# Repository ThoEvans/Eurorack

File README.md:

# Eurorack
Hardware design for Eurorack modular synthesizers

These files contain schematics (.sch) and board layouts (.brd) from AutoDesk Eagle.
Please note that these are simple projects or ideas that are at various stages of completion.

To download an individual file, right click "Raw" and choose "Save link as..."

PCBs available at Pusherman Productions! [Dual LPF PCBs](https://pushermanproductions.com/product/thomas-evans-dual-lp-vcf-pcb-set-fr4-panel/)

## Any questions or comments can be sent to thoevans1994@gmail(dot)com.

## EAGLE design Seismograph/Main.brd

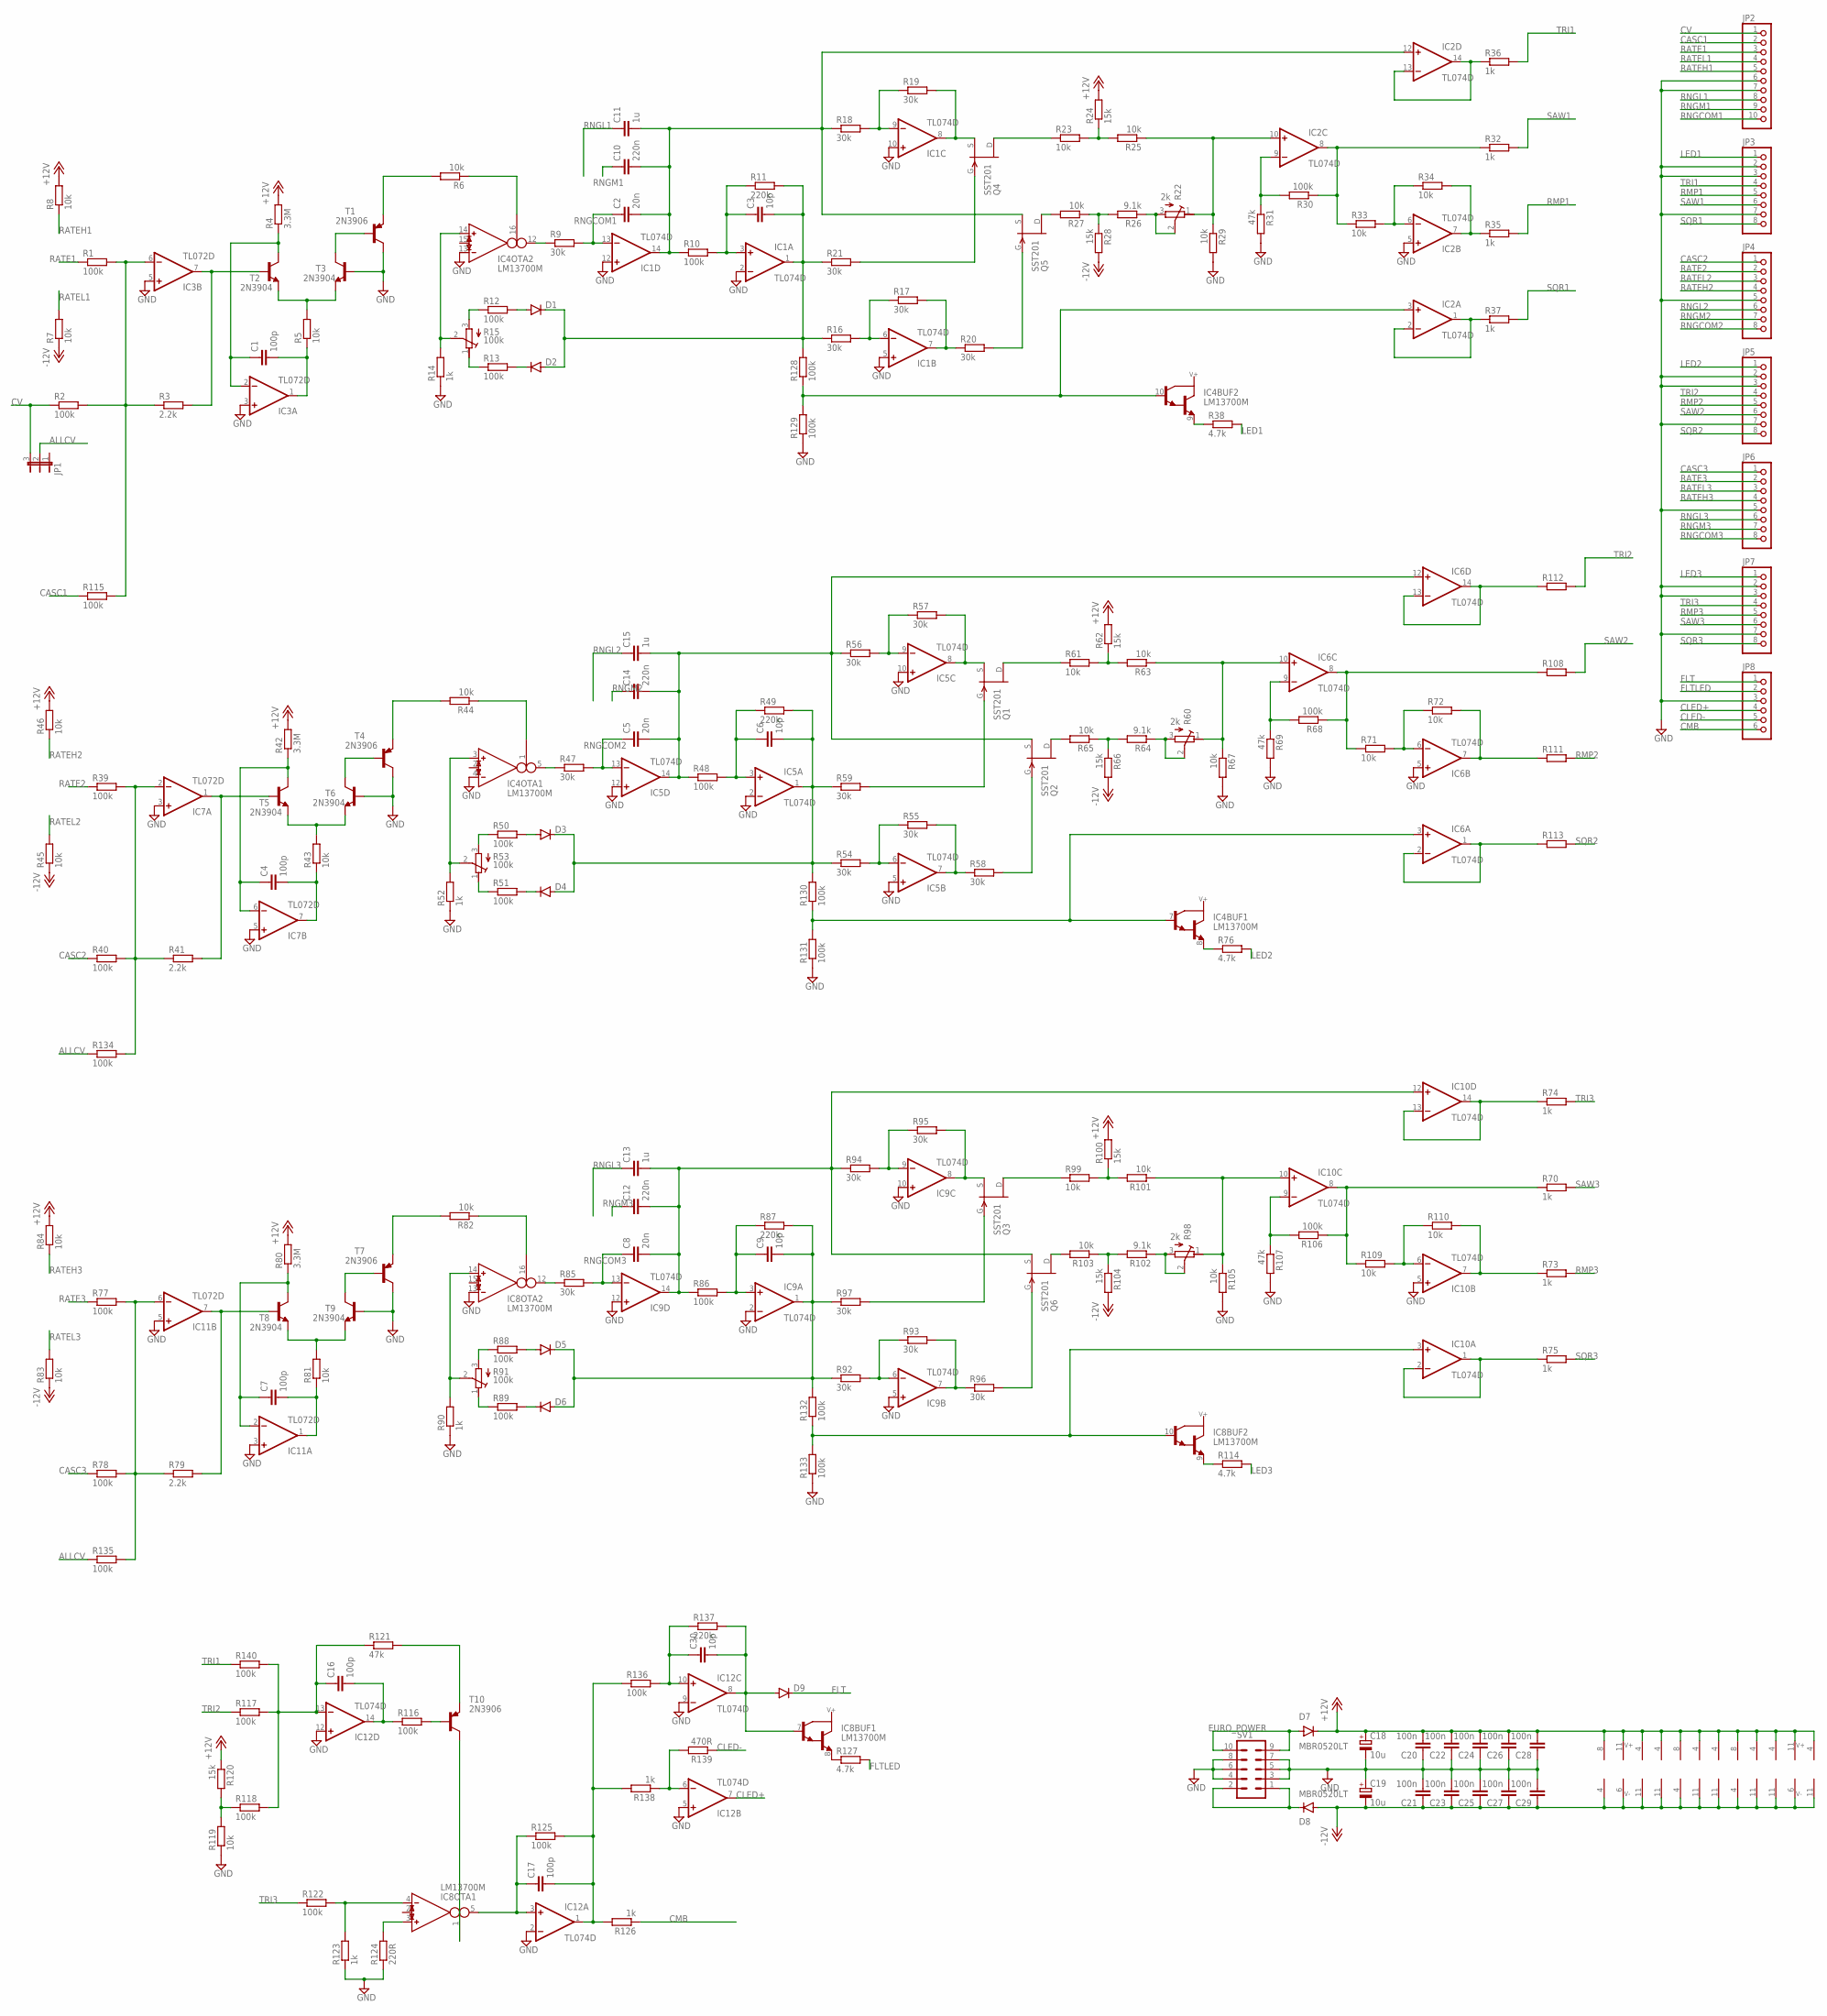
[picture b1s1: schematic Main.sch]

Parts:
C1, C4, C7, C16, C17: 100p; C0805
C2, C5, C8: 20n; C050-025X075
C3, C6, C9, C30: 10p; C0805
C10, C12, C14: 220n; C050-035X075
C11, C13, C15: 1u; C050-045X075
C18, C19: 10u; E2,5-5
C20, C21, C22, C23, C24, C25, C26, C27, C28, C29: 100n; C0805
D1, D2, D3, D4, D5, D6, D9: DIODE-SOD123; SOD123
D7, D8: MBR0520LT; SOD123
IC1, IC2, IC5, IC6, IC9, IC10, IC12: TL074D; SO14
IC3, IC7, IC11: TL072D; SO08
IC4, IC8: LM13700M; SO16
JP1: JP2E; JP2
JP2: PINHD-1X10; 1X10
JP3, JP4, JP5, JP6, JP7: PINHD-1X8; 1X08
JP8: PINHD-1X6; 1X06
Q1, Q2, Q3, Q4, Q5, Q6: SST201; SOT23
R1, R2, R10, R12, R13, R30, R39, R40, R48, R50, R51, R68, R77, R78, R86, R88, R89, R106, R115, R116, R117, R118, R122, R125, R128, R129, R130, R131, R132, R133, R134, R135, R136, R140: 100k; R0805
R3, R41, R79: 2.2k; R0805
R4, R42, R80: 3.3M; R0805
R5, R6, R7, R8, R23, R25, R27, R29, R33, R34, R43, R44, R45, R46, R61, R63, R65, R67, R71, R72, R81, R82, R83, R84, R99, R101, R103, R105, R109, R110, R119: 10k; R0805
R9, R16, R17, R18, R19, R20, R21, R47, R54, R55, R56, R57, R58, R59, R85, R92, R93, R94, R95, R96, R97: 30k; R0805
R11, R49, R87, R137: 220k; R0805
R14, R32, R35, R36, R37, R52, R70, R73, R74, R75, R90, R123, R126, R138: 1k; R0805
R15, R53, R91: 100k; RTRIMT93XB
R22, R60, R98: 2k; RTRIMT93XB
R24, R28, R62, R66, R100, R104, R120: 15k; R0805
R26, R64, R102: 9.1k; R0805
R31, R69, R107, R121: 47k; R0805
R38, R76, R114, R127: 4.7k; R0805
R108, R111, R112, R113: R-EU_R0805; R0805
R124: 220R; R0805
R139: 470R; R0805
SV1: EURO_POWER; EURO_PWR_HEADER_FAT
T1, T4, T7, T10: 2N3906; SOT23-BEC
T2, T3, T5, T6, T8, T9: 2N3904; SOT23-BEC

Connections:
+12V: C18.+, C20.2, C22.2, C24.2, C26.2, C28.2, D7.C, IC1.4 (V+), IC2.4 (V+), IC3.8 (V+), IC4.11 (V+), IC5.4 (V+), IC6.4 (V+), IC7.8 (V+), IC8.11 (V+), IC9.4 (V+), IC10.4 (V+), IC11.8 (V+), IC12.4 (V+), R4.2, R8.2, R24.2, R42.2, R46.2, R62.2, R80.2, R84.2, R100.2, R120.1
-12V: C19.-, C21.1, C23.1, C25.1, C27.1, C29.1, D8.A, IC1.11 (V-), IC2.11 (V-), IC3.4 (V-), IC4.6 (V-), IC5.11 (V-), IC6.11 (V-), IC7.4 (V-), IC8.6 (V-), IC9.11 (V-), IC10.11 (V-), IC11.4 (V-), IC12.11 (V-), R7.1, R28.2, R45.1, R66.2, R83.1, R104.2
ALLCV: JP1.2, R134.1, R135.1
CASC1: JP2.2, R115.1
CASC2: JP4.1, R40.1
CASC3: JP6.1, R78.1
CLED+: IC12.7 (OUT), JP8.4
CLED-: JP8.5, R139.1
CMB: JP8.6, R126.1
CV: JP1.3, JP2.1, R2.1
FLT: D9.C, JP8.1
FLTLED: JP8.2, R127.2
GND: C18.-, C19.+, C20.1, C21.2, C22.1, C23.2, C24.1, C25.2, C26.1, C27.2, C28.1, C29.2, IC1.2 (-IN), IC1.5 (+IN), IC1.10 (+IN), IC1.12 (+IN), IC2.5 (+IN), IC3.3 (+IN), IC3.5 (+IN), IC4.4 (IN_N), IC4.13 (IN_N), IC5.2 (-IN), IC5.5 (+IN), IC5.10 (+IN), IC5.12 (+IN), IC6.5 (+IN), IC7.3 (+IN), IC7.5 (+IN), IC8.13 (IN_N), IC9.2 (-IN), IC9.5 (+IN), IC9.10 (+IN), IC9.12 (+IN), IC10.5 (+IN), IC11.3 (+IN), IC11.5 (+IN), IC12.2 (-IN), IC12.5 (+IN), IC12.9 (-IN), IC12.12 (+IN), JP2.6, JP2.7, JP3.2, JP3.3, JP3.7, JP4.5, JP5.2, JP5.3, JP5.7, JP6.5, JP7.2, JP7.3, JP7.7, JP8.3, R14.1, R29.2, R31.2, R52.1, R67.2, R69.2, R90.1, R105.2, R107.2, R119.1, R123.1, R124.1, R129.1, R131.1, R133.1, SV1.3, SV1.4, SV1.5, SV1.6, SV1.7, SV1.8, T1.C, T3.B, T4.C, T6.B, T7.C, T9.B
LED1: JP3.1, R38.2
LED2: JP5.1, R76.2
LED3: JP7.1, R114.2
unnamed: IC8.8 (E), R127.1
unnamed: C30.1, IC12.10 (+IN), R136.2, R137.1
unnamed: C30.2, D9.A, IC8.7 (B), IC12.8 (OUT), R137.2
unnamed: IC3.6 (-IN), R1.2, R2.2, R3.1, R115.2
unnamed: R5.2, T2.E, T3.E
unnamed: IC3.7 (OUT), R3.2, T2.B
unnamed: C1.1, IC3.2 (-IN), R4.1, T2.C
unnamed: C1.2, IC3.1 (OUT), R5.1
unnamed: T1.B, T3.C
unnamed: D2.C, R13.2
unnamed: R6.2, T1.E
unnamed: IC12.6 (-IN), R138.1, R139.2
unnamed: C16.1, IC12.13 (-IN), R117.2, R118.2, R121.1, R140.2
unnamed: D1.A, R12.2
unnamed: IC4.12 (OUT), R9.1
unnamed: C2.2, C10.2, C11.2, IC1.14 (OUT), IC2.12 (+IN), Q5.2 (S), R10.1, R18.1
unnamed: C3.1, IC1.3 (+IN), R10.2, R11.1
unnamed: IC2.3 (+IN), IC4.10 (B), R128.1, R129.2
unnamed: R12.1, R15.3 (A)
unnamed: R13.1, R15.1 (E)
unnamed: IC4.14 (IN_P), R14.2, R15.2 (S)
unnamed: IC1.6 (-IN), R16.2, R17.1
unnamed: IC1.7 (OUT), R17.2, R20.1
unnamed: IC1.9 (-IN), R18.2, R19.1
unnamed: IC1.8 (OUT), Q4.2 (S), R19.2
unnamed: Q4.3 (G), R21.2
unnamed: Q5.3 (G), R20.2
unnamed: Q4.1 (D), R23.1
unnamed: Q5.1 (D), R27.2
unnamed: R26.2, R27.1, R28.1
unnamed: R23.2, R24.1, R25.2
unnamed: IC2.10 (+IN), R22.1 (E), R25.1, R29.1
unnamed: R22.2 (S), R22.3 (A), R26.1
unnamed: IC7.2 (-IN), R39.2, R40.2, R41.1, R134.2
unnamed: IC2.9 (-IN), R30.2, R31.1
unnamed: IC2.8 (OUT), R30.1, R32.1, R33.1
unnamed: IC2.7 (OUT), R34.2, R35.1
unnamed: IC2.6 (-IN), R33.2, R34.1
unnamed: IC2.13 (-IN), IC2.14 (OUT), R36.1
unnamed: IC2.1 (OUT), IC2.2 (-IN), R37.1
unnamed: IC7.1 (OUT), R41.2, T5.B
unnamed: C4.1, IC7.6 (-IN), R42.1, T5.C
unnamed: IC4.9 (E), R38.1
unnamed: IC4.16 (I_BIAS), R6.1
unnamed: R43.2, T5.E, T6.E
unnamed: C4.2, IC7.7 (OUT), R43.1
unnamed: T4.B, T6.C
unnamed: D4.C, R51.2
unnamed: D3.A, R50.2
unnamed: IC4.5 (OUT), R47.1
unnamed: C5.2, C14.2, C15.2, IC5.14 (OUT), IC6.12 (+IN), Q2.2 (S), R48.1, R56.1
unnamed: C6.1, IC5.3 (+IN), R48.2, R49.1
unnamed: IC4.7 (B), IC6.3 (+IN), R130.1, R131.2
unnamed: R50.1, R53.3 (A)
unnamed: R51.1, R53.1 (E)
unnamed: IC4.3 (IN_P), R52.2, R53.2 (S)
unnamed: IC5.6 (-IN), R54.2, R55.1
unnamed: IC5.7 (OUT), R55.2, R58.1
unnamed: IC5.9 (-IN), R56.2, R57.1
unnamed: IC5.8 (OUT), Q1.2 (S), R57.2
unnamed: Q1.3 (G), R59.2
unnamed: Q2.3 (G), R58.2
unnamed: Q1.1 (D), R61.1
unnamed: Q2.1 (D), R65.2
unnamed: R64.2, R65.1, R66.1
unnamed: R61.2, R62.1, R63.2
unnamed: IC6.10 (+IN), R60.1 (E), R63.1, R67.1
unnamed: R60.2 (S), R60.3 (A), R64.1
unnamed: IC6.9 (-IN), R68.2, R69.1
unnamed: IC6.8 (OUT), R68.1, R71.1, R108.1
unnamed: IC6.7 (OUT), R72.2, R111.1
unnamed: IC6.6 (-IN), R71.2, R72.1
unnamed: IC6.13 (-IN), IC6.14 (OUT), R112.1
unnamed: IC6.1 (OUT), IC6.2 (-IN), R113.1
unnamed: R118.1, R119.2, R120.2
unnamed: IC4.8 (E), R76.1
unnamed: R44.2, T4.E
unnamed: IC4.1 (I_BIAS), R44.1
unnamed: IC11.6 (-IN), R77.2, R78.2, R79.1, R135.2
unnamed: IC11.7 (OUT), R79.2, T8.B
unnamed: C7.1, IC11.2 (-IN), R80.1, T8.C
unnamed: R81.2, T8.E, T9.E
unnamed: C7.2, IC11.1 (OUT), R81.1
unnamed: T7.B, T9.C
unnamed: D6.C, R89.2
unnamed: D5.A, R88.2
unnamed: IC8.12 (OUT), R85.1
unnamed: C8.2, C12.2, C13.2, IC9.14 (OUT), IC10.12 (+IN), Q6.2 (S), R86.1, R94.1
unnamed: C9.1, IC9.3 (+IN), R86.2, R87.1
unnamed: IC8.10 (B), IC10.3 (+IN), R132.1, R133.2
unnamed: R88.1, R91.3 (A)
unnamed: R89.1, R91.1 (E)
unnamed: IC8.14 (IN_P), R90.2, R91.2 (S)
unnamed: IC9.6 (-IN), R92.2, R93.1
unnamed: IC9.7 (OUT), R93.2, R96.1
unnamed: IC9.9 (-IN), R94.2, R95.1
unnamed: IC9.8 (OUT), Q3.2 (S), R95.2
unnamed: Q3.3 (G), R97.2
unnamed: Q6.3 (G), R96.2
unnamed: Q3.1 (D), R99.1
unnamed: Q6.1 (D), R103.2
unnamed: R102.2, R103.1, R104.1
unnamed: R99.2, R100.1, R101.2
unnamed: IC10.10 (+IN), R98.1 (E), R101.1, R105.1
unnamed: R98.2 (S), R98.3 (A), R102.1
unnamed: IC10.9 (-IN), R106.2, R107.1
unnamed: IC10.8 (OUT), R70.1, R106.1, R109.1
unnamed: IC10.7 (OUT), R73.1, R110.2
unnamed: IC10.6 (-IN), R109.2, R110.1
unnamed: IC10.13 (-IN), IC10.14 (OUT), R74.1
unnamed: IC10.1 (OUT), IC10.2 (-IN), R75.1
unnamed: IC8.9 (E), R114.1
unnamed: R82.2, T7.E
unnamed: IC8.16 (I_BIAS), R82.1
unnamed: C16.2, IC12.14 (OUT), R116.1
unnamed: R116.2, T10.B
unnamed: R121.2, T10.E
unnamed: IC8.1 (I_BIAS), T10.C
unnamed: IC8.3 (IN_P), R124.2
unnamed: C17.2, IC12.1 (OUT), R125.2, R126.2, R136.1, R138.2
unnamed: IC8.4 (IN_N), R122.2, R123.2
unnamed: C17.1, IC8.5 (OUT), IC12.3 (+IN), R125.1
unnamed: C9.2, D5.C, D6.A, IC9.1 (OUT), R87.2, R92.1, R97.1, R132.2
unnamed: C6.2, D3.C, D4.A, IC5.1 (OUT), R49.2, R54.1, R59.1, R130.2
unnamed: C3.2, D1.C, D2.A, IC1.1 (OUT), R11.2, R16.1, R21.1, R128.2
unnamed: D7.A, SV1.9, SV1.10
unnamed: D8.C, SV1.1, SV1.2
RATE1: JP2.3, R1.1
RATE2: JP4.2, R39.1
RATE3: JP6.2, R77.1
RATEH1: JP2.5, R8.1
RATEH2: JP4.4, R46.1
RATEH3: JP6.4, R84.1
RATEL1: JP2.4, R7.2
RATEL2: JP4.3, R45.2
RATEL3: JP6.3, R83.2
RMP1: JP3.5, R35.2
RMP2: JP5.5, R111.2
RMP3: JP7.5, R73.2
RNGCOM1: C2.1, IC1.13 (-IN), JP2.10, R9.2
RNGCOM2: C5.1, IC5.13 (-IN), JP4.8, R47.2
RNGCOM3: C8.1, IC9.13 (-IN), JP6.8, R85.2
RNGL1: C11.1, JP2.8
RNGL2: C15.1, JP4.6
RNGL3: C13.1, JP6.6
RNGM1: C10.1, JP2.9
RNGM2: C14.1, JP4.7
RNGM3: C12.1, JP6.7
SAW1: JP3.6, R32.2
SAW2: JP5.6, R108.2
SAW3: JP7.6, R70.2
SQR1: JP3.8, R37.2
SQR2: JP5.8, R113.2
SQR3: JP7.8, R75.2
TRI1: JP3.4, R36.2, R140.1
TRI2: JP5.4, R112.2, R117.1
TRI3: JP7.4, R74.2, R122.1

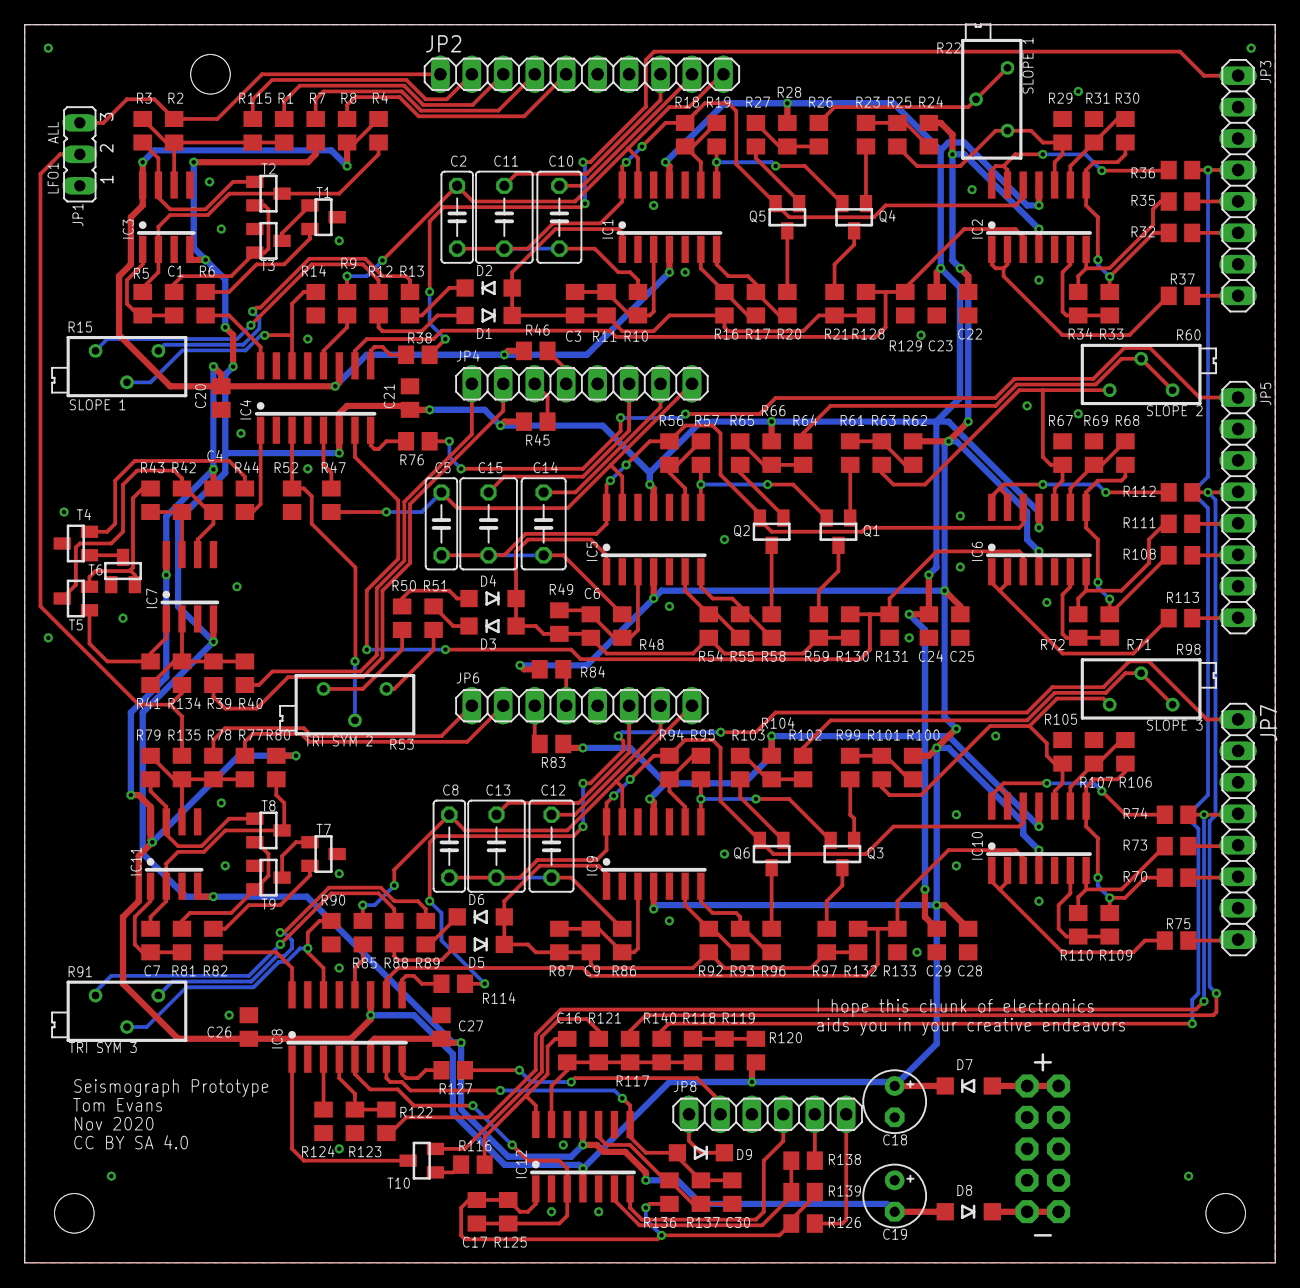
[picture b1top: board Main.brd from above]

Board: 2 copper layers, 101.0 x 100.0 mm, 216 parts (1 on the bottom side), 173 nets.

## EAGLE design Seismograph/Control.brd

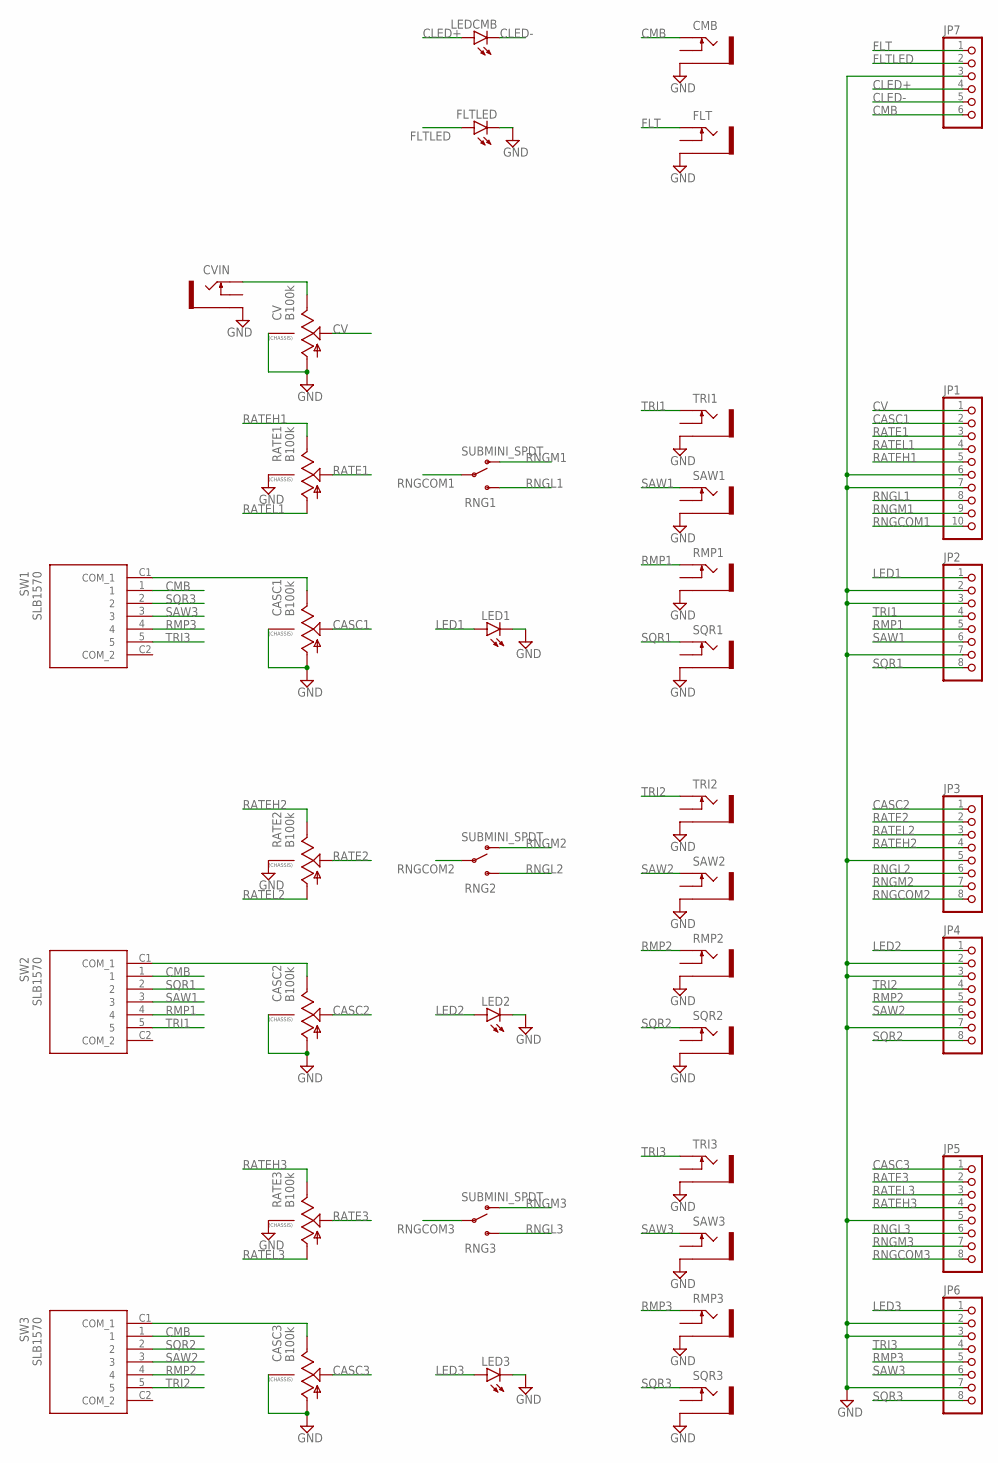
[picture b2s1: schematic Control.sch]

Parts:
CASC1, CASC2, CASC3: B100k; 9MM_SNAP-IN_POT
CMB: THONKICONNNEW; WQP-PJ301M-12_JACK
CV: B100k; 9MM_SNAP-IN_POT
CVIN: THONKICONNNEW; WQP-PJ301M-12_JACK
FLT: THONKICONNNEW; WQP-PJ301M-12_JACK
FLTLED: LED3MM
JP1: PINHD-1X10; 1X10
JP2, JP3, JP4, JP5, JP6: PINHD-1X8; 1X08
JP7: PINHD-1X6; 1X06
LED1, LED2, LED3: LED3MM
LEDCMB: LED3MM
RATE1, RATE2, RATE3: B100k; 9MM_SNAP-IN_POT
RMP1, RMP2, RMP3: THONKICONNNEW; WQP-PJ301M-12_JACK
RNG1, RNG2, RNG3: SUBMINI_SPDT; SUBMINI_TOGGLE
SAW1, SAW2, SAW3: THONKICONNNEW; WQP-PJ301M-12_JACK
SQR1, SQR2, SQR3: THONKICONNNEW; WQP-PJ301M-12_JACK
SW1, SW2, SW3: SLB1570
TRI1, TRI2, TRI3: THONKICONNNEW; WQP-PJ301M-12_JACK

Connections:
CASC1: CASC1.2 (S), JP1.2
CASC2: CASC2.2 (S), JP3.1
CASC3: CASC3.2 (S), JP5.1
CLED+: JP7.4, LEDCMB.A
CLED-: JP7.5, LEDCMB.K (C)
CMB: CMB.P$1_TIP (TIP), JP7.6, SW1.1, SW2.1, SW3.1
CV: CV.2 (S), JP1.1
FLT: FLT.P$1_TIP (TIP), JP7.1
FLTLED: FLTLED.A, JP7.2
GND: CASC1.1 (A), CASC1.CHASSIS1, CASC1.CHASSIS2, CASC2.1 (A), CASC2.CHASSIS1, CASC2.CHASSIS2, CASC3.1 (A), CASC3.CHASSIS1, CASC3.CHASSIS2, CMB.P$3_SLEEVE (SLEEVE), CV.1 (A), CV.CHASSIS1, CV.CHASSIS2, CVIN.P$3_SLEEVE (SLEEVE), FLT.P$3_SLEEVE (SLEEVE), FLTLED.K (C), JP1.6, JP1.7, JP2.2, JP2.3, JP2.7, JP3.5, JP4.2, JP4.3, JP4.7, JP5.5, JP6.2, JP6.3, JP6.7, JP7.3, LED1.K (C), LED2.K (C), LED3.K (C), RATE1.CHASSIS1, RATE1.CHASSIS2, RATE2.CHASSIS1, RATE2.CHASSIS2, RATE3.CHASSIS1, RATE3.CHASSIS2, RMP1.P$3_SLEEVE (SLEEVE), RMP2.P$3_SLEEVE (SLEEVE), RMP3.P$3_SLEEVE (SLEEVE), SAW1.P$3_SLEEVE (SLEEVE), SAW2.P$3_SLEEVE (SLEEVE), SAW3.P$3_SLEEVE (SLEEVE), SQR1.P$3_SLEEVE (SLEEVE), SQR2.P$3_SLEEVE (SLEEVE), SQR3.P$3_SLEEVE (SLEEVE), TRI1.P$3_SLEEVE (SLEEVE), TRI2.P$3_SLEEVE (SLEEVE), TRI3.P$3_SLEEVE (SLEEVE)
LED1: JP2.1, LED1.A
LED2: JP4.1, LED2.A
LED3: JP6.1, LED3.A
unnamed: CV.3 (E), CVIN.P$1_TIP (TIP)
unnamed: CASC1.3 (E), SW1.C1 (COM_1)
unnamed: CASC2.3 (E), SW2.C1 (COM_1)
unnamed: CASC3.3 (E), SW3.C1 (COM_1)
RATE1: JP1.3, RATE1.2 (S)
RATE2: JP3.2, RATE2.2 (S)
RATE3: JP5.2, RATE3.2 (S)
RATEH1: JP1.5, RATE1.3 (E)
RATEH2: JP3.4, RATE2.3 (E)
RATEH3: JP5.4, RATE3.3 (E)
RATEL1: JP1.4, RATE1.1 (A)
RATEL2: JP3.3, RATE2.1 (A)
RATEL3: JP5.3, RATE3.1 (A)
RMP1: JP2.5, RMP1.P$1_TIP (TIP), SW2.4
RMP2: JP4.5, RMP2.P$1_TIP (TIP), SW3.4
RMP3: JP6.5, RMP3.P$1_TIP (TIP), SW1.4
RNGCOM1: JP1.10, RNG1.COM (COMMON)
RNGCOM2: JP3.8, RNG2.COM (COMMON)
RNGCOM3: JP5.8, RNG3.COM (COMMON)
RNGL1: JP1.8, RNG1.3 (S)
RNGL2: JP3.6, RNG2.3 (S)
RNGL3: JP5.6, RNG3.3 (S)
RNGM1: JP1.9, RNG1.1 (O)
RNGM2: JP3.7, RNG2.1 (O)
RNGM3: JP5.7, RNG3.1 (O)
SAW1: JP2.6, SAW1.P$1_TIP (TIP), SW2.3
SAW2: JP4.6, SAW2.P$1_TIP (TIP), SW3.3
SAW3: JP6.6, SAW3.P$1_TIP (TIP), SW1.3
SQR1: JP2.8, SQR1.P$1_TIP (TIP), SW2.2
SQR2: JP4.8, SQR2.P$1_TIP (TIP), SW3.2
SQR3: JP6.8, SQR3.P$1_TIP (TIP), SW1.2
TRI1: JP2.4, SW2.5, TRI1.P$1_TIP (TIP)
TRI2: JP4.4, SW3.5, TRI2.P$1_TIP (TIP)
TRI3: JP6.4, SW1.5, TRI3.P$1_TIP (TIP)

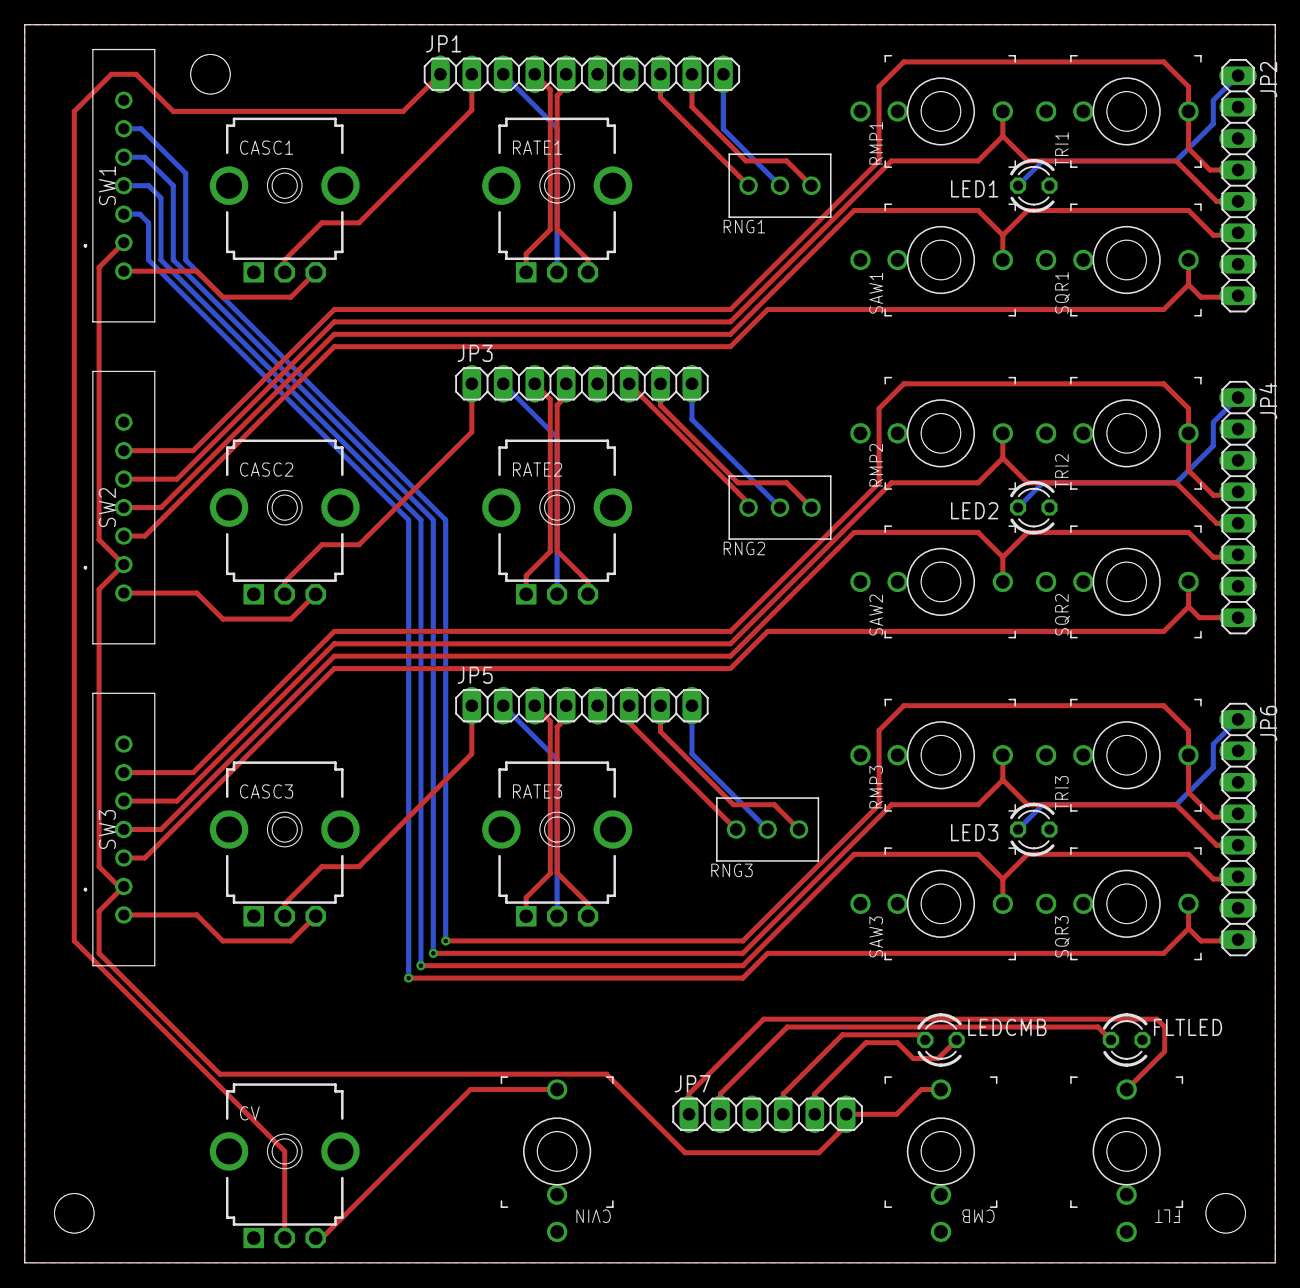
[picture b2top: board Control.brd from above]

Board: 2 copper layers, 101.0 x 100.0 mm, 40 parts (0 on the bottom side), 47 nets.

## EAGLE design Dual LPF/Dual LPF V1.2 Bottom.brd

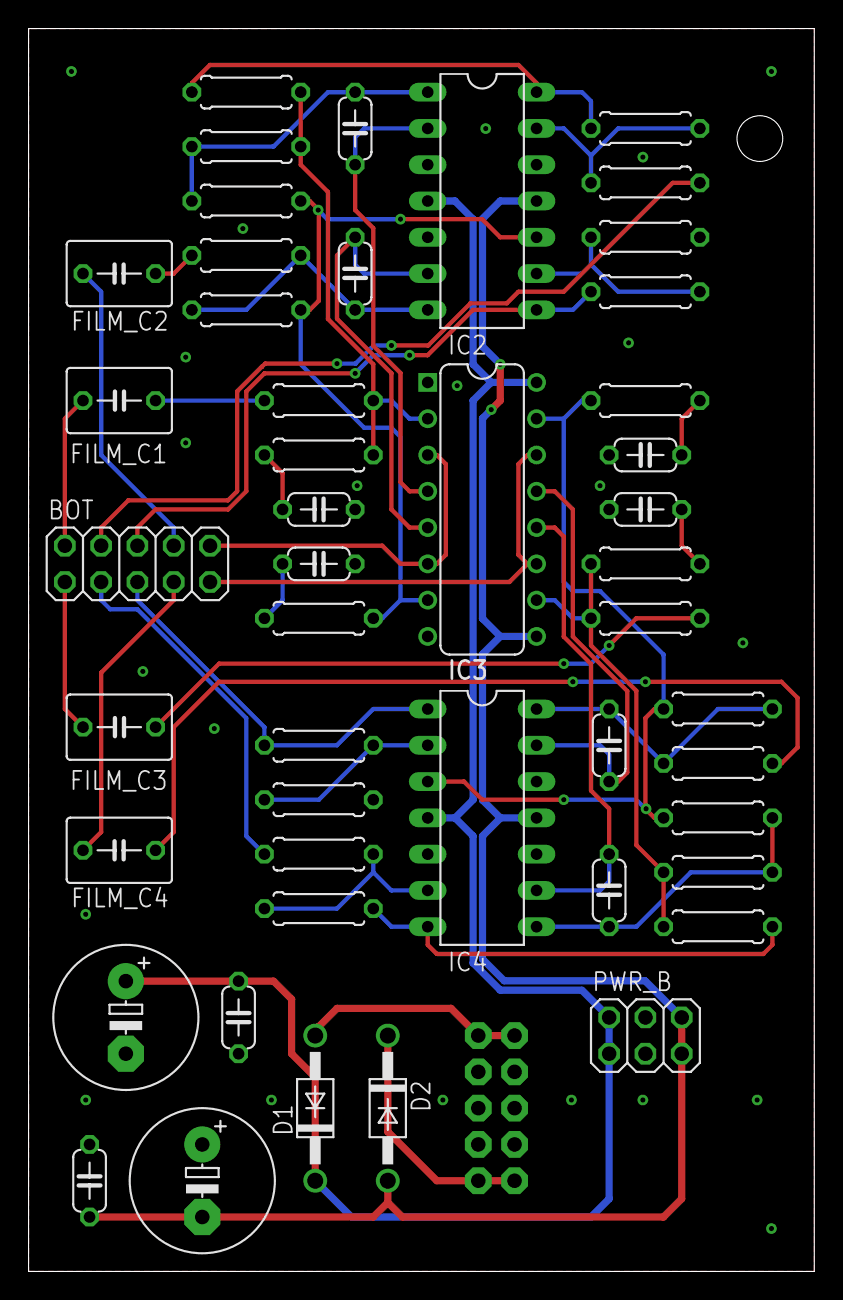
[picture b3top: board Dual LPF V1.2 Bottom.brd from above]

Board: 2 copper layers, 55.0 x 87.0 mm, 48 parts (1 on the bottom side), 41 nets.

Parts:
BOT: 2X05
C1, C2: 10u; E5-10,5
C3, C4: 100n; C050-024X044
C5, C7, C9, C11: 470p; C050-024X044
C6, C8, C10, C12: 220p; C050-024X044
D1, D2: 1N4004; DO41-10
FILM_C1, FILM_C2, FILM_C3, FILM_C4: 1uF; C050-045X075
IC2, IC4: TL074; DIL14
IC3: V2164; DIP-16
PWR_B: 2X03
PWR_RIBBON: EURO_PWR_HEADER_FAT
R18, R29, R30, R41: 47k; 0207/7
R19, R22, R25, R31, R34, R37: 470R; 0207/7
R20, R21, R23, R27, R32, R33, R35, R39: 30k; 0207/7
R24, R36: 1k; 0207/7
R26, R38: 220k; 0207/7
R28, R40: 100k; 0207/7

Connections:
GND: C1.-, C2.+, C3.2, C4.1, C5.2, C7.2, C9.2, C11.2, IC2.3, IC2.5, IC2.12, IC3.8, IC4.5, IC4.10, IC4.12, PWR_B.3, PWR_B.4, PWR_RIBBON.3, PWR_RIBBON.4, PWR_RIBBON.5, PWR_RIBBON.6, PWR_RIBBON.7, PWR_RIBBON.8, R25.2, R37.2
IC_CV1_B: BOT.10, IC3.3, IC3.6
IC_CV3_B: BOT.9, IC3.11, IC3.14
IC_IN1: IC3.2, R18.2, R19.2, R20.1, R29.1
IC_IN2: IC2.10, IC3.7, R21.2, R22.2, R23.1
IC_IN3: IC3.10, R30.2, R31.2, R32.1, R41.1
IC_IN4: IC3.15, IC4.3, R33.2, R34.2, R35.1
IC_OUT1: C6.2, IC2.2, IC3.4
IC_OUT2: C8.2, IC2.6, IC3.5
IC_OUT3: C10.2, IC3.12, IC4.9
IC_OUT4: C12.2, IC3.13, IC4.13
IN1_B: BOT.2, FILM_C1.1
IN2_B: BOT.1, FILM_C3.1
unnamed: C6.1, IC2.1, R20.2, R21.1
unnamed: FILM_C1.2, R18.1
unnamed: C5.1, R19.1
unnamed: C7.1, R22.1
unnamed: C8.1, IC2.7, R23.2, R24.1
unnamed: FILM_C2.1, R24.2
unnamed: IC2.9, R25.1, R26.2
unnamed: IC2.14, R28.1, R29.2
unnamed: IC2.13, R27.1, R28.2
unnamed: D1.A, PWR_RIBBON.9, PWR_RIBBON.10
unnamed: FILM_C3.2, R30.1
unnamed: C9.1, R31.1
unnamed: C10.1, IC4.8, R32.2, R33.1
unnamed: C11.1, R34.1
unnamed: C12.1, IC4.14, R35.2, R36.1
unnamed: FILM_C4.1, R36.2
unnamed: D2.C, PWR_RIBBON.1, PWR_RIBBON.2
unnamed: IC4.2, R37.1, R38.2
unnamed: IC4.6, R39.1, R40.2
unnamed: IC4.7, R40.1, R41.2
OUT1_B: BOT.8, FILM_C2.2
OUT2_B: BOT.7, FILM_C4.2
RESIN1_B: BOT.6, IC2.8, R26.1
RESIN2_B: BOT.5, IC4.1, R38.1
RESOUT1_B: BOT.4, R27.2
RESOUT2_B: BOT.3, R39.2
V+: C1.+, C3.1, D1.C, IC2.4, IC3.16, IC4.4, PWR_B.1, PWR_B.2
V-: C2.-, C4.2, D2.A, IC2.11, IC3.9, IC4.11, PWR_B.5, PWR_B.6

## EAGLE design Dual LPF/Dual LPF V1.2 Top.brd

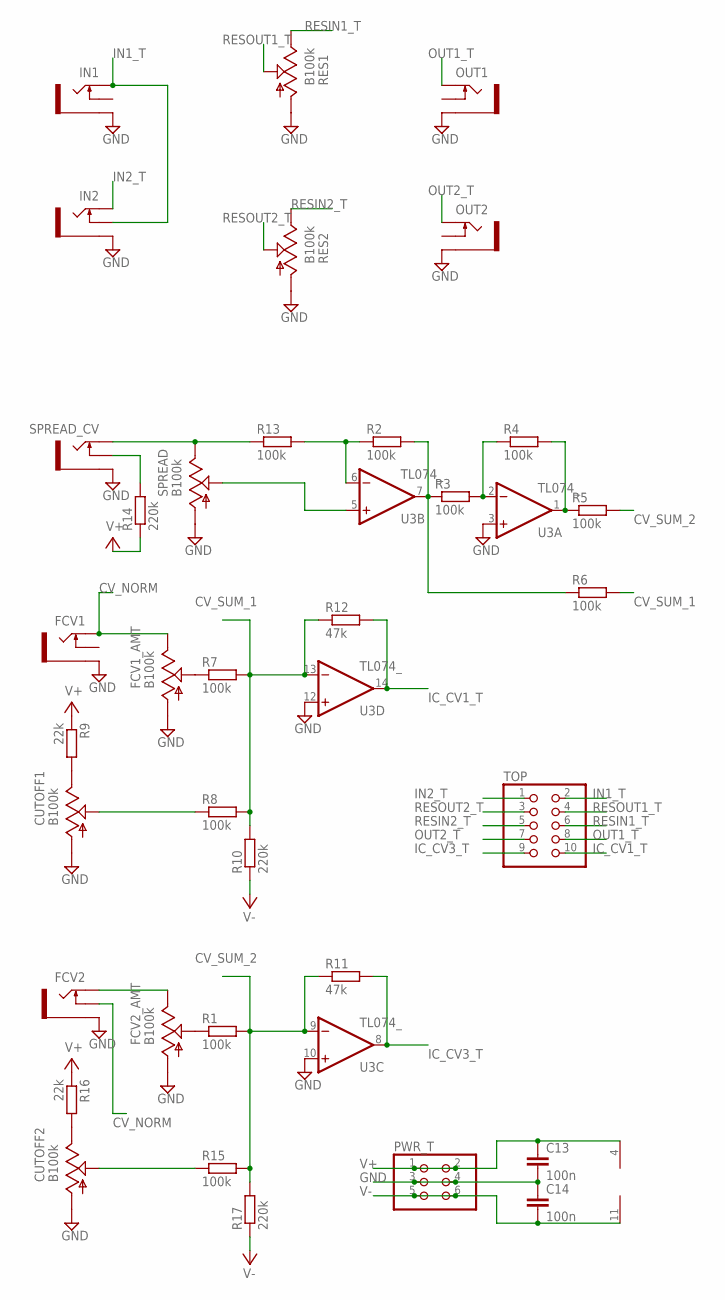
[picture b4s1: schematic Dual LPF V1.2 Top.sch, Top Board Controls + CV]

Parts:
C13, C14: 100n; C050-024X044
CUTOFF1, CUTOFF2: B100k; 9MM_SNAP-IN_POT
FCV1, FCV2: THONKICONNNEW; WQP-PJ301M-12_JACK
FCV1_AMT, FCV2_AMT: B100k; 9MM_SNAP-IN_POT
IN1, IN2: THONKICONNNEW; WQP-PJ301M-12_JACK
OUT1, OUT2: THONKICONNNEW; WQP-PJ301M-12_JACK
PWR_T: PINHD-2X3; 2X03
R1, R2, R3, R4, R5, R6, R7, R8, R13, R15: 100k; 0207/7
R9, R16: 22k; 0207/7
R10, R14, R17: 220k; 0207/7
R11, R12: 47k; 0207/7
RES1, RES2: B100k; 9MM_SNAP-IN_POT
SPREAD: B100k; 9MM_SNAP-IN_POT
SPREAD_CV: THONKICONNNEW; WQP-PJ301M-12_JACK
TOP: PINHD-2X5; 2X05
U3: TL074_; DIL14

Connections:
CV_NORM: FCV1.P$1_TIP (TIP), FCV1_AMT.3 (E), FCV2.P$2_SWITCH (SWITCH)
CV_SUM_1: R6.2, R7.2, R8.2, R10.2, R12.1, U3.13 (-IN)
CV_SUM_2: R1.2, R5.2, R11.1, R15.2, R17.2, U3.9 (-IN)
GND: C13.2, C14.1, CUTOFF1.1 (A), CUTOFF2.1 (A), FCV1.P$3_SLEEVE (SLEEVE), FCV1_AMT.1 (A), FCV2.P$3_SLEEVE (SLEEVE), FCV2_AMT.1 (A), IN1.P$3_SLEEVE (SLEEVE), IN2.P$3_SLEEVE (SLEEVE), OUT1.P$3_SLEEVE (SLEEVE), OUT2.P$3_SLEEVE (SLEEVE), PWR_T.3, PWR_T.4, RES1.1 (A), RES2.1 (A), SPREAD.1 (A), SPREAD_CV.P$3_SLEEVE (SLEEVE), U3.3 (+IN), U3.10 (+IN), U3.12 (+IN)
IC_CV1_T: R12.2, TOP.10, U3.14 (OUT)
IC_CV3_T: R11.2, TOP.9, U3.8 (OUT)
IN1_T: IN1.P$1_TIP (TIP), IN2.P$2_SWITCH (SWITCH), TOP.2
IN2_T: IN2.P$1_TIP (TIP), TOP.1
unnamed: FCV2_AMT.2 (S), R1.1
unnamed: R2.1, R13.2, U3.6 (-IN)
unnamed: R2.2, R3.1, R6.1, U3.7 (OUT)
unnamed: R3.2, R4.1, U3.2 (-IN)
unnamed: R4.2, R5.1, U3.1 (OUT)
unnamed: R14.2, SPREAD_CV.P$2_SWITCH (SWITCH)
unnamed: SPREAD.2 (S), U3.5 (+IN)
unnamed: R13.1, SPREAD.3 (E), SPREAD_CV.P$1_TIP (TIP)
unnamed: FCV1_AMT.2 (S), R7.1
unnamed: CUTOFF1.2 (S), R8.1
unnamed: CUTOFF1.3 (E), R9.2
unnamed: CUTOFF2.2 (S), R15.1
unnamed: CUTOFF2.3 (E), R16.2
unnamed: FCV2.P$1_TIP (TIP), FCV2_AMT.3 (E)
OUT1_T: OUT1.P$1_TIP (TIP), TOP.8
OUT2_T: OUT2.P$1_TIP (TIP), TOP.7
RESIN1_T: RES1.3 (E), TOP.6
RESIN2_T: RES2.3 (E), TOP.5
RESOUT1_T: RES1.2 (S), TOP.4
RESOUT2_T: RES2.2 (S), TOP.3
V+: C13.1, PWR_T.1, PWR_T.2, R9.1, R14.1, R16.1, U3.4 (V+)
V-: C14.2, PWR_T.5, PWR_T.6, R10.1, R17.1, U3.11 (V-)

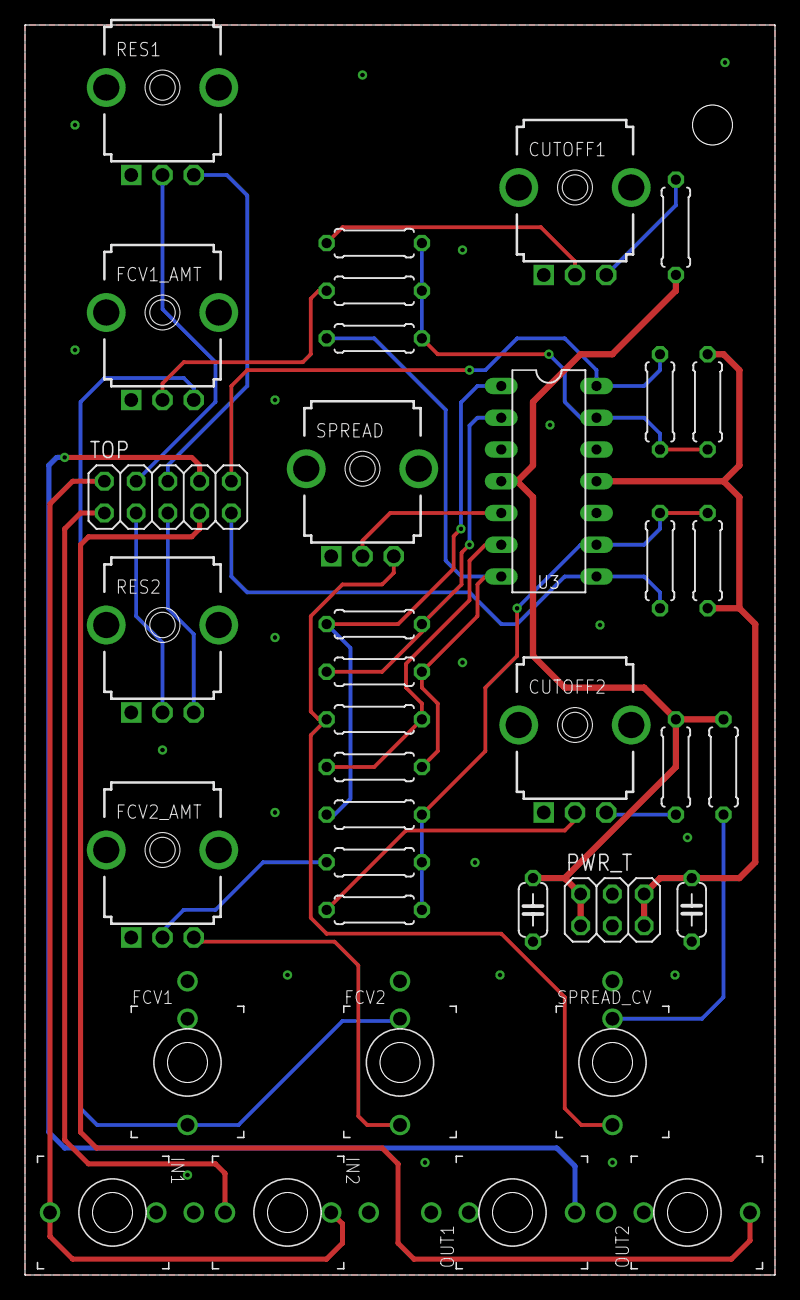
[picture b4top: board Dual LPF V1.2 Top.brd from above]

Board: 2 copper layers, 60.0 x 100.0 mm, 36 parts (0 on the bottom side), 30 nets.

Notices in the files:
Dual LPF/Dual LPF V1.2 Bottom.brd:
CC BY 4.0
Seismograph/Main.brd:
CC BY SA 4.0
